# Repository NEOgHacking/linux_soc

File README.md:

# linux_soc
Linux_soc is a very advanced linux capable module for the hackxpansion console, it consists of a F1C100s soc with integrated stacked ddr1 ram. It also contains a atmega 328p microcontroller, the same found on the arduino uno. It has its own usb ttl converter for programming. In total there are 2 usb ports one for the linux soc and one for the atmega. The pcb also contains a triple buck converter to meet the different requirements that are required by the linux soc

# Design
The linux soc module was designed in Kicad, i choose kicad because its opensource and its rich nature of features.

## Schematic

## PCB
The pcb consist of 4 layers for better power management and routing, it was otherwise also just impossible to do with all the different power rails.

## Case
The case was made in onshape. Here is the public link to access the document [link](https://cad.onshape.com/documents/23acd3255b900cc5b85fa1fc/w/7ef244823df79fb773706f50/e/0ac388d0a99e7c2b0060239b?renderMode=0&uiState=6abee2b1fc9f4045824befa1) The case itself was made pretty complex also because of the complexity of the board, with no space for mouthing holes i had to resort to mounting it by clips.

## Software

- `firmware/` — Hackxpansion console driver (`linux-soc-driver`, Embassy /
  `xpanse-api` on the RP2354). Opens the Linux terminal UART (console GPIO5/6
  at 115200 8N1) and registers a `LinuxSocHandle` for apps. Build with
  `cargo build` in `firmware/` (defaults to the RP2354 target).
  See `firmware/README.md`.
- `linux/` — Mainline U-Boot + Linux for the onboard F1C100s with console on
  UART0 (`ttyS0`, 115200 8N1, PE0/PE1 -> J1 P10/P11). Board DTS
  `suniv-f1c100s-linux_soc.dts`, `boot.cmd`, kernel fragment and `build.sh`
  (U-Boot `licheepi_nano_defconfig` + Linux `multi_v5_defconfig`).
  See `linux/README.md`.

## BOM

| Place | Cost |
|-------|------|
| LCSC | $72.61 |
| JLCPCB | $10.36 |
| **Total** | **$82.97** |

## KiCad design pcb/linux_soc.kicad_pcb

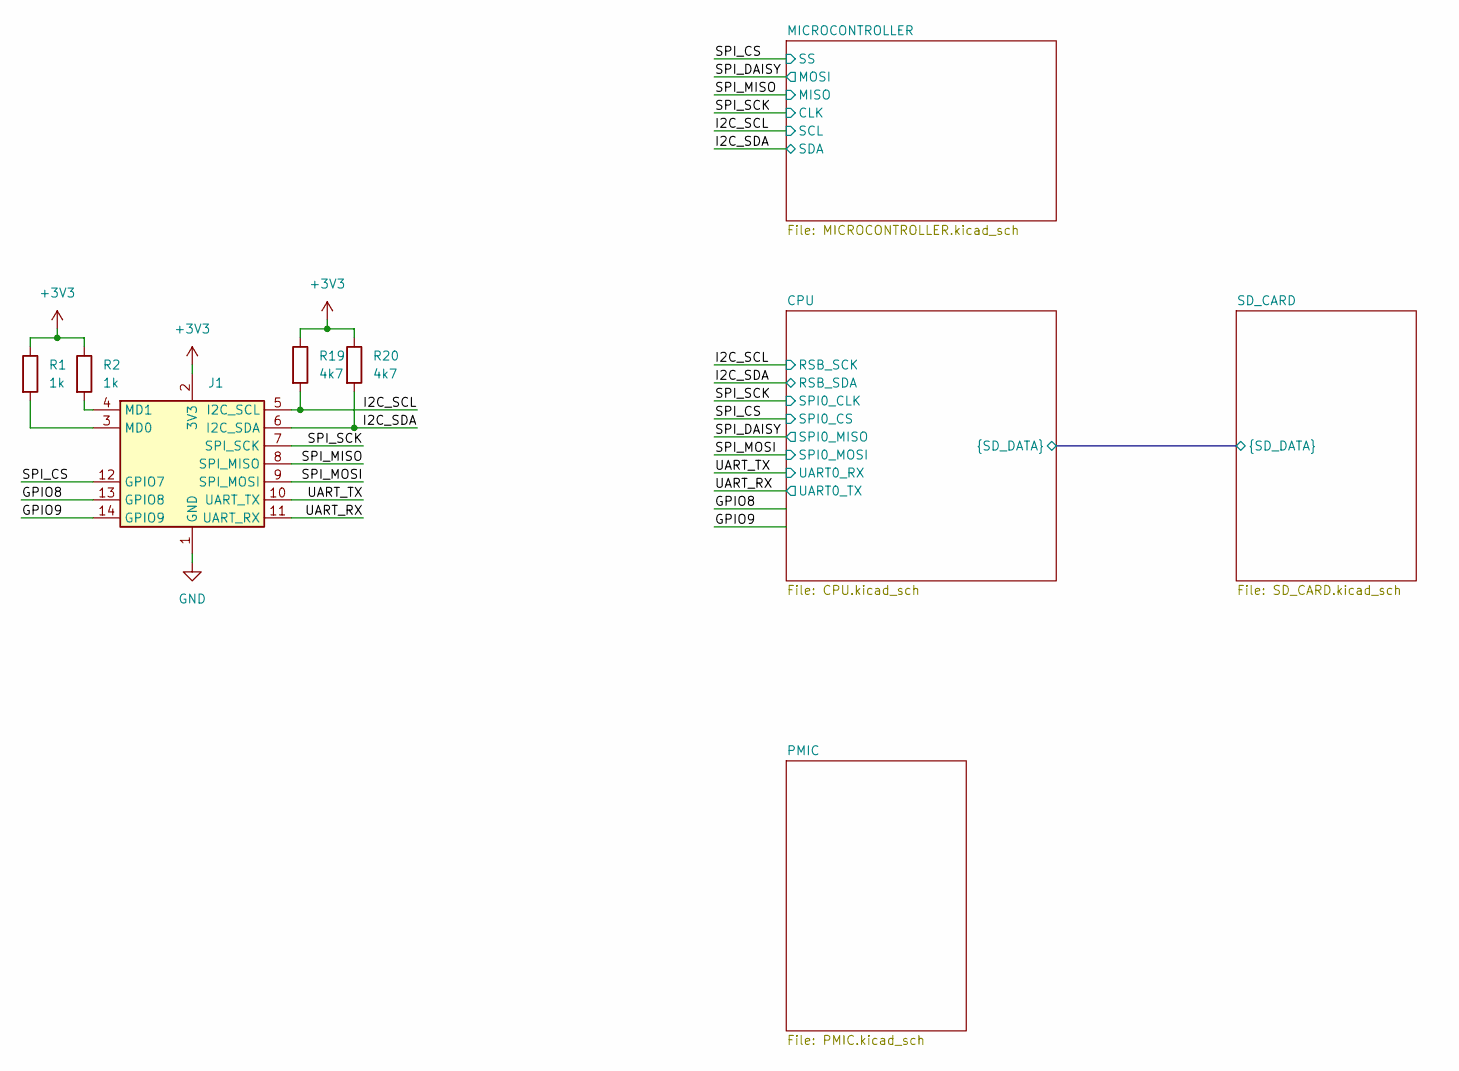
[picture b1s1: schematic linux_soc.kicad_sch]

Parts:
J1: PinHeader_2x07_P2.54mm_Horizontal; LCSC# C706888
R1, R2: 1k; R_0402_1005Metric; LCSC# C106235
R19, R20: 4k7; R_0402_1005Metric; LCSC# C105871

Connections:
+3V3: J1.2 (3V3), R1.1, R2.1, R19.1, R20.1; also elsewhere on the board
/GPIO8: J1.13 (GPIO8)
/GPIO9: J1.14 (GPIO9)
/I2C_SCL: J1.5 (I2C_SCL), R19.2; also elsewhere on the board
/I2C_SDA: J1.6 (I2C_SDA), R20.2; also elsewhere on the board
/SPI_CS: J1.12 (GPIO7); also elsewhere on the board
/SPI_MISO: J1.8 (SPI_MISO); also elsewhere on the board
/SPI_MOSI: J1.9 (SPI_MOSI); also elsewhere on the board
/SPI_SCK: J1.7 (SPI_SCK); also elsewhere on the board
/UART_RX: J1.11 (UART_RX); also elsewhere on the board
/UART_TX: J1.10 (UART_TX); also elsewhere on the board
GND: J1.1 (GND); also elsewhere on the board
unnamed: J1.3 (MD0), R1.2
unnamed: J1.4 (MD1), R2.2

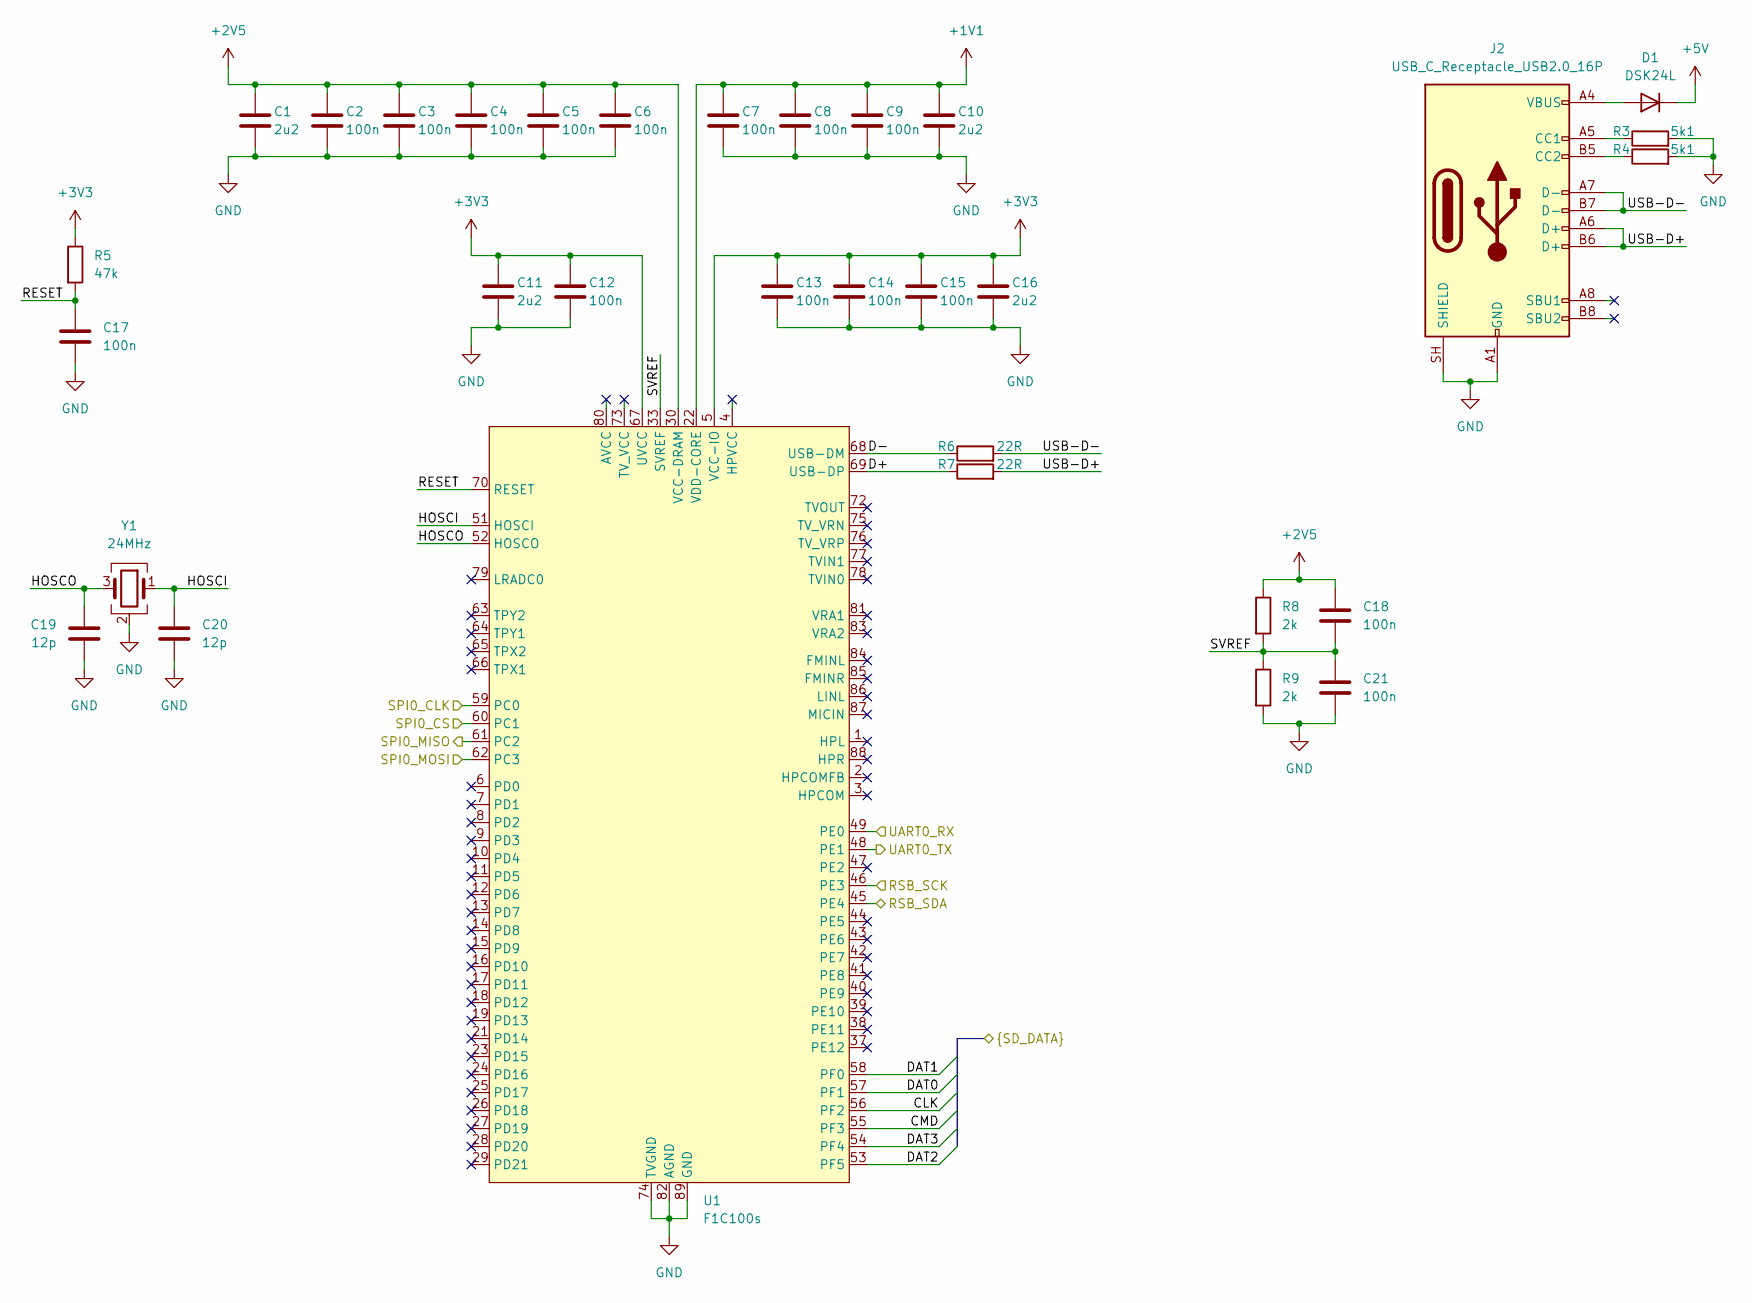
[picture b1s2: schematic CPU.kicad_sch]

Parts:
C1, C10, C11, C16: 2u2; C_0402_1005Metric; LCSC# C12530
C2, C3, C4, C5, C6, C7, C8, C9, C12, C13, C14, C15, C17, C18, C21: 100n; C_0402_1005Metric; LCSC# C1525
C19, C20: 12p; C_0402_1005Metric; LCSC# C26406
D1: DSK24L; D_SOD-123F; LCSC# C19272974
J2: USB_C_Receptacle_USB2.0_16P; USB_C_Receptacle_GCT_USB4105-xx-A_16P_TopMnt_Horizontal; LCSC# C165948
R3, R4: 5k1; R_0402_1005Metric; LCSC# C105872
R5: 47k; R_0402_1005Metric; LCSC# C93943
R6, R7: 22R; R_0402_1005Metric; LCSC# C114765
R8, R9: 2k; R_0402_1005Metric; LCSC# C60488
U1: F1C100s; QFN-88_EP_10x10_Pitch0.4mm; LCSC# C1511928
Y1: 24MHz; Crystal_SMD_2016-4Pin_2.0x1.6mm; LCSC# C7303340

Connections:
+1V1: C7.1, C8.1, C9.1, C10.1, U1.22 (VDD-CORE), U1.35 (VDD-CORE), U1.71 (VDD-CORE); also elsewhere on the board
+2V5: C1.1, C2.1, C3.1, C4.1, C5.1, C6.1, C18.1, R8.1, U1.30 (VCC-DRAM), U1.31 (VCC-DRAM), U1.32 (VCC-DRAM), U1.34 (VCC-DRAM), U1.36 (VCC-DRAM); also elsewhere on the board
+3V3: C11.1, C12.1, C13.1, C14.1, C15.1, C16.1, R5.1, U1.5 (VCC-IO), U1.20 (VCC-IO), U1.50 (VCC-IO), U1.67 (UVCC); also elsewhere on the board
+5V: D1.1 (K); also elsewhere on the board
/CPU/CLK: U1.56 (PF2); also elsewhere on the board
/CPU/CMD: U1.55 (PF3); also elsewhere on the board
/CPU/D+: R7.1, U1.69 (USB-DP)
/CPU/D-: R6.1, U1.68 (USB-DM)
/CPU/DAT0: U1.57 (PF1); also elsewhere on the board
/CPU/DAT1: U1.58 (PF0); also elsewhere on the board
/CPU/DAT2: U1.53 (PF5); also elsewhere on the board
/CPU/DAT3: U1.54 (PF4); also elsewhere on the board
/CPU/HOSCI: C20.1, U1.51 (HOSCI), Y1.1
/CPU/HOSCO: C19.1, U1.52 (HOSCO), Y1.3
/CPU/RESET: C17.1, R5.2, U1.70 (RESET)
/CPU/SVREF: C18.2, C21.1, R8.2, R9.1, U1.33 (SVREF)
/CPU/USB-D+: J2.A6 (D+), J2.B6 (D+), R7.2
/CPU/USB-D-: J2.A7 (D-), J2.B7 (D-), R6.2
/I2C_SCL: U1.46 (PE3); also elsewhere on the board
/I2C_SDA: U1.45 (PE4); also elsewhere on the board
/SPI_CS: U1.60 (PC1); also elsewhere on the board
/SPI_DAISY: U1.61 (PC2); also elsewhere on the board
/SPI_MOSI: U1.62 (PC3); also elsewhere on the board
/SPI_SCK: U1.59 (PC0); also elsewhere on the board
/UART_RX: U1.48 (PE1); also elsewhere on the board
/UART_TX: U1.49 (PE0); also elsewhere on the board
GND: C1.2, C2.2, C3.2, C4.2, C5.2, C6.2, C7.2, C8.2, C9.2, C10.2, C11.2, C12.2, C13.2, C14.2, C15.2, C16.2, C17.2, C19.2, C20.2, C21.2, J2.A1 (GND), J2.A12 (GND), J2.B1 (GND), J2.B12 (GND), J2.SH (SHIELD), R3.2, R4.2, R9.2, U1.74 (TVGND), U1.82 (AGND), U1.89 (GND), Y1.2 (G), Y1.4 (G); also elsewhere on the board
unnamed: D1.2 (A), J2.A4 (VBUS), J2.A9 (VBUS), J2.B4 (VBUS), J2.B9 (VBUS)
unnamed: J2.A5 (CC1), R3.1
unnamed: J2.B5 (CC2), R4.1

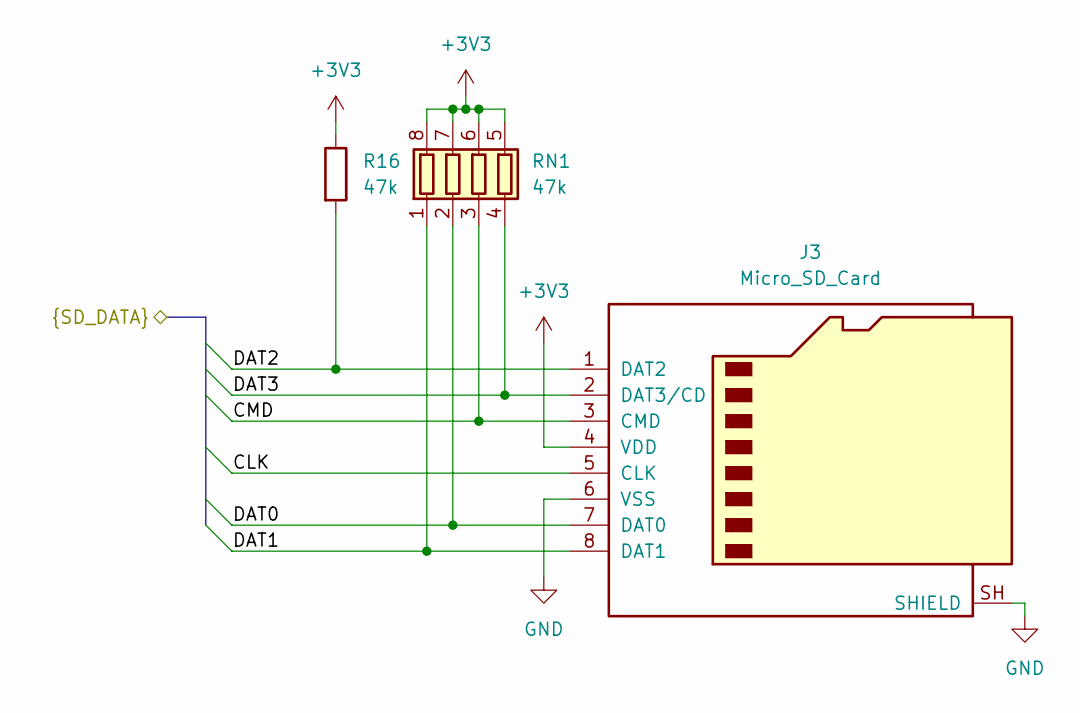
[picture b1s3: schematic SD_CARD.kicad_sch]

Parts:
J3: Micro_SD_Card; microSD_HC_Hirose_DM3AT-SF-PEJM5; LCSC# C114218
R16: 47k; R_0402_1005Metric; LCSC# C93943
RN1: 47k; R_Array_Convex_4x0402; LCSC# C326859

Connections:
+3V3: J3.4 (VDD), R16.1, RN1.5 (R4.2), RN1.6 (R3.2), RN1.7 (R2.2), RN1.8 (R1.2); also elsewhere on the board
/CPU/CLK: J3.5 (CLK); also elsewhere on the board
/CPU/CMD: J3.3 (CMD), RN1.3 (R3.1); also elsewhere on the board
/CPU/DAT0: J3.7 (DAT0), RN1.2 (R2.1); also elsewhere on the board
/CPU/DAT1: J3.8 (DAT1), RN1.1 (R1.1); also elsewhere on the board
/CPU/DAT2: J3.1 (DAT2), R16.2; also elsewhere on the board
/CPU/DAT3: J3.2 (DAT3/CD), RN1.4 (R4.1); also elsewhere on the board
GND: J3.6 (VSS), J3.SH (SHIELD); also elsewhere on the board

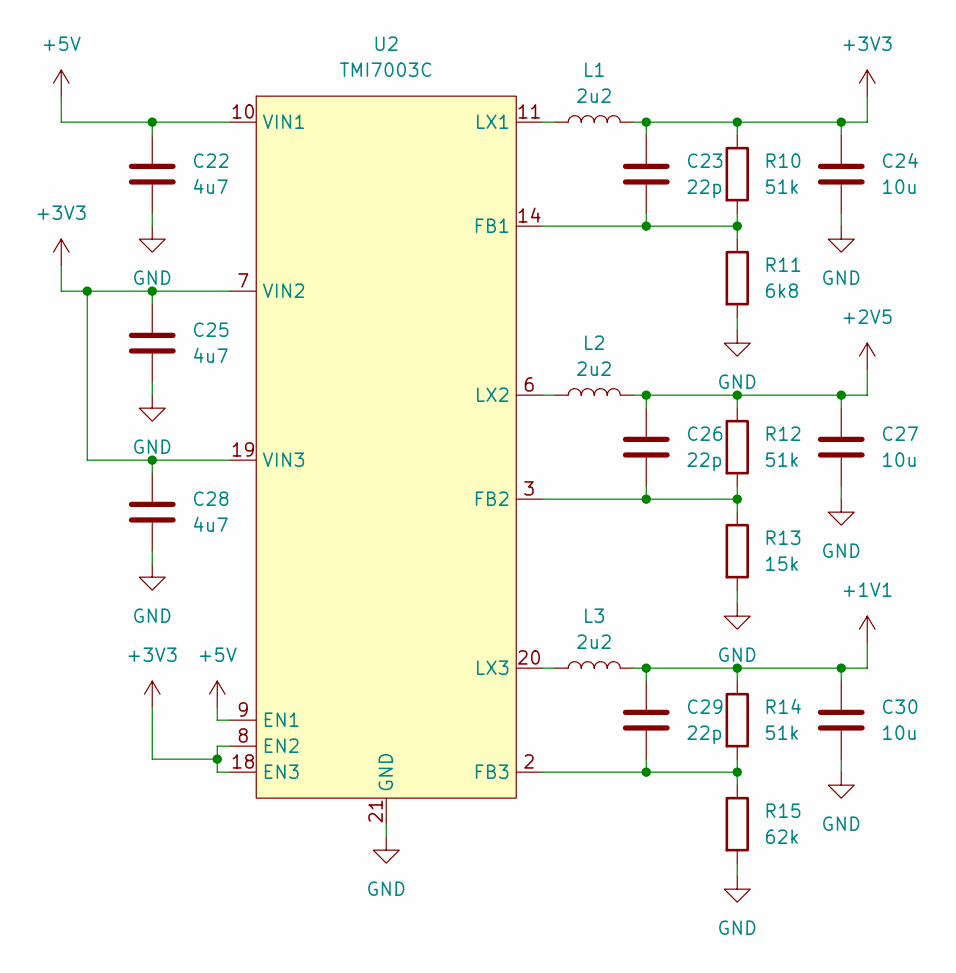
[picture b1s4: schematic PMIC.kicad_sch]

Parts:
C22, C25, C28: 4u7; C_0402_1005Metric; LCSC# C368809
C23, C26, C29: 22p; C_0402_1005Metric; LCSC# C70464
C24, C27, C30: 10u; C_0603_1608Metric; LCSC# C19702
L1, L2, L3: 2u2; L_0805_2012Metric; LCSC# C22471111
R10, R12, R14: 51k; R_0402_1005Metric; LCSC# C107229
R11: 6k8; R_0402_1005Metric; LCSC# C93940
R13: 15k; R_0402_1005Metric; LCSC# C114761
R15: 62k; R_0402_1005Metric; LCSC# C137950
U2: TMI7003C; QFN-20-1EP_3x3mm_P0.4mm_EP1.65x1.65mm; LCSC# C840566

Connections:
+1V1: C29.1, C30.1, L3.2, R14.1; also elsewhere on the board
+2V5: C26.1, C27.1, L2.2, R12.1; also elsewhere on the board
+3V3: C23.1, C24.1, C25.1, C28.1, L1.2, R10.1, U2.7 (VIN2), U2.8 (EN2), U2.18 (EN3), U2.19 (VIN3); also elsewhere on the board
+5V: C22.1, U2.9 (EN1), U2.10 (VIN1); also elsewhere on the board
GND: C22.2, C24.2, C25.2, C27.2, C28.2, C30.2, R11.2, R13.2, R15.2, U2.21 (GND); also elsewhere on the board
unnamed: C23.2, R10.2, R11.1, U2.14 (FB1)
unnamed: C26.2, R12.2, R13.1, U2.3 (FB2)
unnamed: C29.2, R14.2, R15.1, U2.2 (FB3)
unnamed: L1.1, U2.11 (LX1)
unnamed: L2.1, U2.6 (LX2)
unnamed: L3.1, U2.20 (LX3)

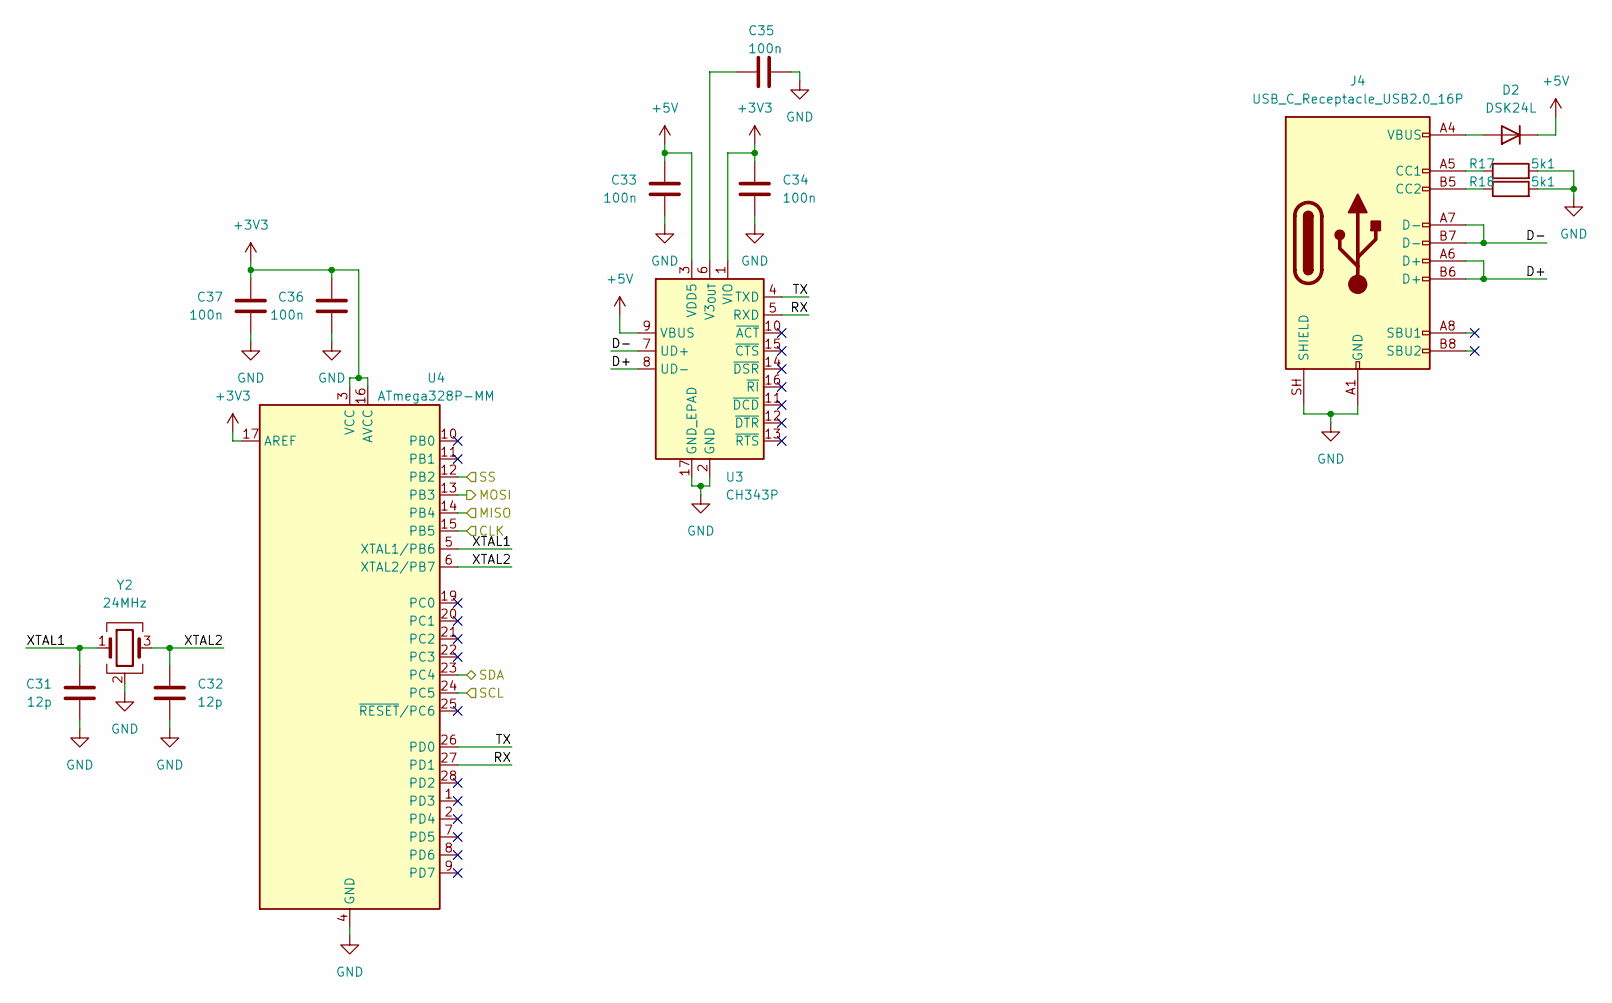
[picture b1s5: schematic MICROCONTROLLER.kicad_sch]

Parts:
C31, C32: 12p; C_0402_1005Metric; LCSC# C26406
C33, C34, C35, C36, C37: 100n; C_0402_1005Metric; LCSC# C1525
D2: DSK24L; D_SOD-123F; LCSC# C19272974
J4: USB_C_Receptacle_USB2.0_16P; USB_C_Receptacle_Vertical; LCSC# C7450621
R17, R18: 5k1; R_0402_1005Metric; LCSC# C105872
U3: CH343P; WCH_QFN-16-1EP_3x3mm_P0.5mm_EP1.8x1.8mm; LCSC# C2846043
U4: ATmega328P-MM; QFN-28-1EP_4x4mm_P0.45mm_EP2.4x2.4mm; LCSC# C2651959
Y2: 24MHz; Crystal_SMD_2016-4Pin_2.0x1.6mm; LCSC# C7303340

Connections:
+3V3: C34.1, C36.1, C37.1, U3.1 (VIO), U4.3 (VCC), U4.16 (AVCC), U4.17 (AREF); also elsewhere on the board
+5V: C33.1, D2.1 (K), U3.3 (VDD5), U3.9 (VBUS); also elsewhere on the board
/I2C_SCL: U4.24 (PC5); also elsewhere on the board
/I2C_SDA: U4.23 (PC4); also elsewhere on the board
/MICROCONTROLLER/D+: J4.A6 (D+), J4.B6 (D+), U3.8 (UD-)
/MICROCONTROLLER/D-: J4.A7 (D-), J4.B7 (D-), U3.7 (UD+)
/MICROCONTROLLER/RX: U3.5 (RXD), U4.27 (PD1)
/MICROCONTROLLER/TX: U3.4 (TXD), U4.26 (PD0)
/MICROCONTROLLER/XTAL1: C31.1, U4.5 (XTAL1/PB6), Y2.1
/MICROCONTROLLER/XTAL2: C32.1, U4.6 (XTAL2/PB7), Y2.3
/SPI_CS: U4.12 (PB2); also elsewhere on the board
/SPI_DAISY: U4.13 (PB3); also elsewhere on the board
/SPI_MISO: U4.14 (PB4); also elsewhere on the board
/SPI_SCK: U4.15 (PB5); also elsewhere on the board
GND: C31.2, C32.2, C33.2, C34.2, C35.1, C36.2, C37.2, J4.A1 (GND), J4.A12 (GND), J4.B1 (GND), J4.B12 (GND), J4.SH (SHIELD), R17.2, R18.2, U3.2 (GND), U3.17 (GND_EPAD), U4.4 (GND), U4.18 (GND), U4.29 (GND), Y2.2 (G), Y2.4 (G); also elsewhere on the board
unnamed: D2.2 (A), J4.A4 (VBUS), J4.A9 (VBUS), J4.B4 (VBUS), J4.B9 (VBUS)
unnamed: J4.A5 (CC1), R17.1
unnamed: J4.B5 (CC2), R18.1
unnamed: C35.2, U3.6 (V3_{OUT})

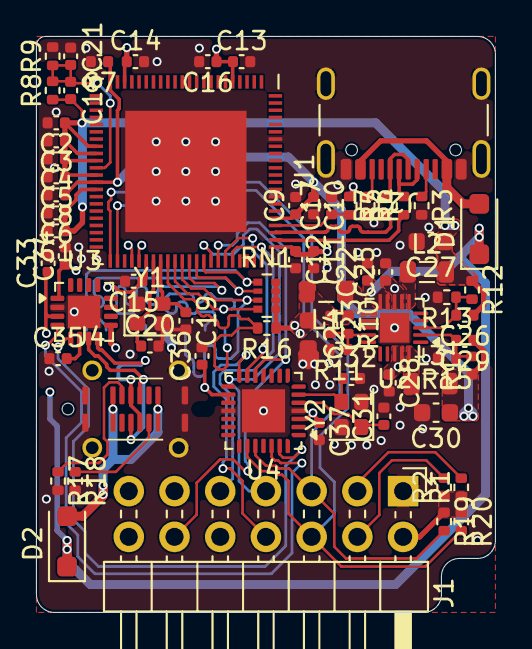
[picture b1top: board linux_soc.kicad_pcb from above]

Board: 4 copper layers, 25.5 x 32.0 mm, 73 parts (1 on the bottom side), 49 nets.

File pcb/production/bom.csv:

Designator,Footprint,Quantity,Value,LCSC Part #
"C1, C10, C11, C16",0402,4,2u2,
"C12, C13, C14, C15, C17, C18, C2, C21, C3, C33, C34, C35, C36, C37, C4, C5, C6, C7, C8, C9",0402,20,100n,
"C19, C20, C31, C32",0402,4,C,
"C22, C25, C28",0402,3,4u7,
"C23, C26, C29",0402,3,22p,
"C24, C27, C30",0603,3,10u,
"D1, D2",D_SOD-123F,2,DSK24L,
J1,PinHeader_2x07_P2.54mm_Horizontal,1,~,
J2,USB_C_Receptacle_GCT_USB4105-xx-A_16P_TopMnt_Horizontal,1,USB_C_Receptacle_USB2.0_16P,
J3,microSD_HC_Hirose_DM3AT-SF-PEJM5,1,Micro_SD_Card,
J4,USB_C_Receptacle_Vertical,1,USB_C_Receptacle_USB2.0_16P,
"L1, L2, L3",0805,3,2u2,
"R1, R2",0402,2,1k,
"R10, R12, R14",0402,3,51k,
R11,0402,1,6k8,
R13,0402,1,15k,
R15,0402,1,62k,
"R16, R5",0402,2,47k,
"R17, R18, R3, R4",0402,4,5k1,
"R19, R20",0402,2,4k7,
"R6, R7",0402,2,22R,
"R8, R9",0402,2,2k,
RN1,R_Array_Convex_4x0402,1,47k,
U1,QFN-88_EP_10x10_Pitch0.4mm,1,F1C100s,
U2,QFN-20-1EP_3x3mm_P0.4mm_EP1.65x1.65mm,1,TMI7003C,
U3,WCH_QFN-16-1EP_3x3mm_P0.5mm_EP1.8x1.8mm,1,CH343P,
U4,QFN-28-1EP_4x4mm_P0.45mm_EP2.4x2.4mm,1,ATmega328P-MM,
"Y1, Y2",Crystal_SMD_2016-4Pin_2.0x1.6mm,2,24MHz,

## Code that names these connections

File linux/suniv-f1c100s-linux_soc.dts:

// Device tree for the linux_soc board (Allwinner F1C100s).
// UART console: UART0 on PE0/PE1 -> J1 P10/P11, 115200 8N1.
//
// Based on mainline suniv-f1c100s.dtsi + the licheepi-nano reference
// (linux/arch/arm/boot/dts/allwinner/suniv-f1c100s-licheepi-nano.dts).
// Installed by build.sh into linux/arch/arm/boot/dts/allwinner/ and built
// with multi_v5_defconfig (ARMv5 base; sunxi_defconfig cannot build suniv).
//
// Wiring verified from pcb/*.kicad_sch:
//   CPU.UART0_TX/RX -> top UART0_TX/RX -> J1.UART_TX/RX (pins 10/11)
//   SoC pins PE0/PE1, pinctrl uart0_pe_pins (func 5), base 0x01C25000.
//   SD card on MMC0 (standard PF0-PF5), USB D+/D- to USB-C.
//   24MHz crystal (HOSCI/HOSCO), 32MB stacked DDR1 at 0x80000000.

/dts-v1/;
#include "suniv-f1c100s.dtsi"

/ {
	model = "linux_soc (F1C100s)";
	compatible = "linux-soc,linux-soc", "allwinner,suniv-f1c100s";

	aliases {
		mmc0 = &mmc0;
		serial0 = &uart0;
	};

	chosen {
		stdout-path = "serial0:115200n8";
		bootargs = "console=ttyS0,115200 earlycon=uart,mmio32,0x01c25000 console=tty0 root=/dev/mmcblk0p2 rootwait rw";
	};

	memory@80000000 {
		device_type = "memory";
		reg = <0x80000000 0x2000000>; /* 32M */
	};
};

&uart0 {
	pinctrl-names = "default";
	pinctrl-0 = <&uart0_pe_pins>;
	status = "okay";
};

/* SD card slot (SD_CARD.kicad_sch: DAT0-3, CMD, CLK on MMC0/PF).
 * No card-detect pin is wired on this board, so poll like licheepi-nano
 * instead of guessing a cd-gpios pin (a wrong guess can hang boot). */
&mmc0 {
	broken-cd;
	bus-width = <4>;
	disable-wp;
	status = "okay";
};

/* USB OTG (CPU.kicad_sch: USB D+/D-). suniv has a single musb OTG
 * controller + phy, no EHCI/OHCI blocks. */
&otg_sram {
	status = "okay";
};

&usb_otg {
	dr_mode = "otg";
	status = "okay";
};

&usbphy {
	status = "okay";
};

/* SPI0 goes to the J1 edge / ATmega daisy chain; enable when needed. */
&spi0 {
	status = "disabled";
};
